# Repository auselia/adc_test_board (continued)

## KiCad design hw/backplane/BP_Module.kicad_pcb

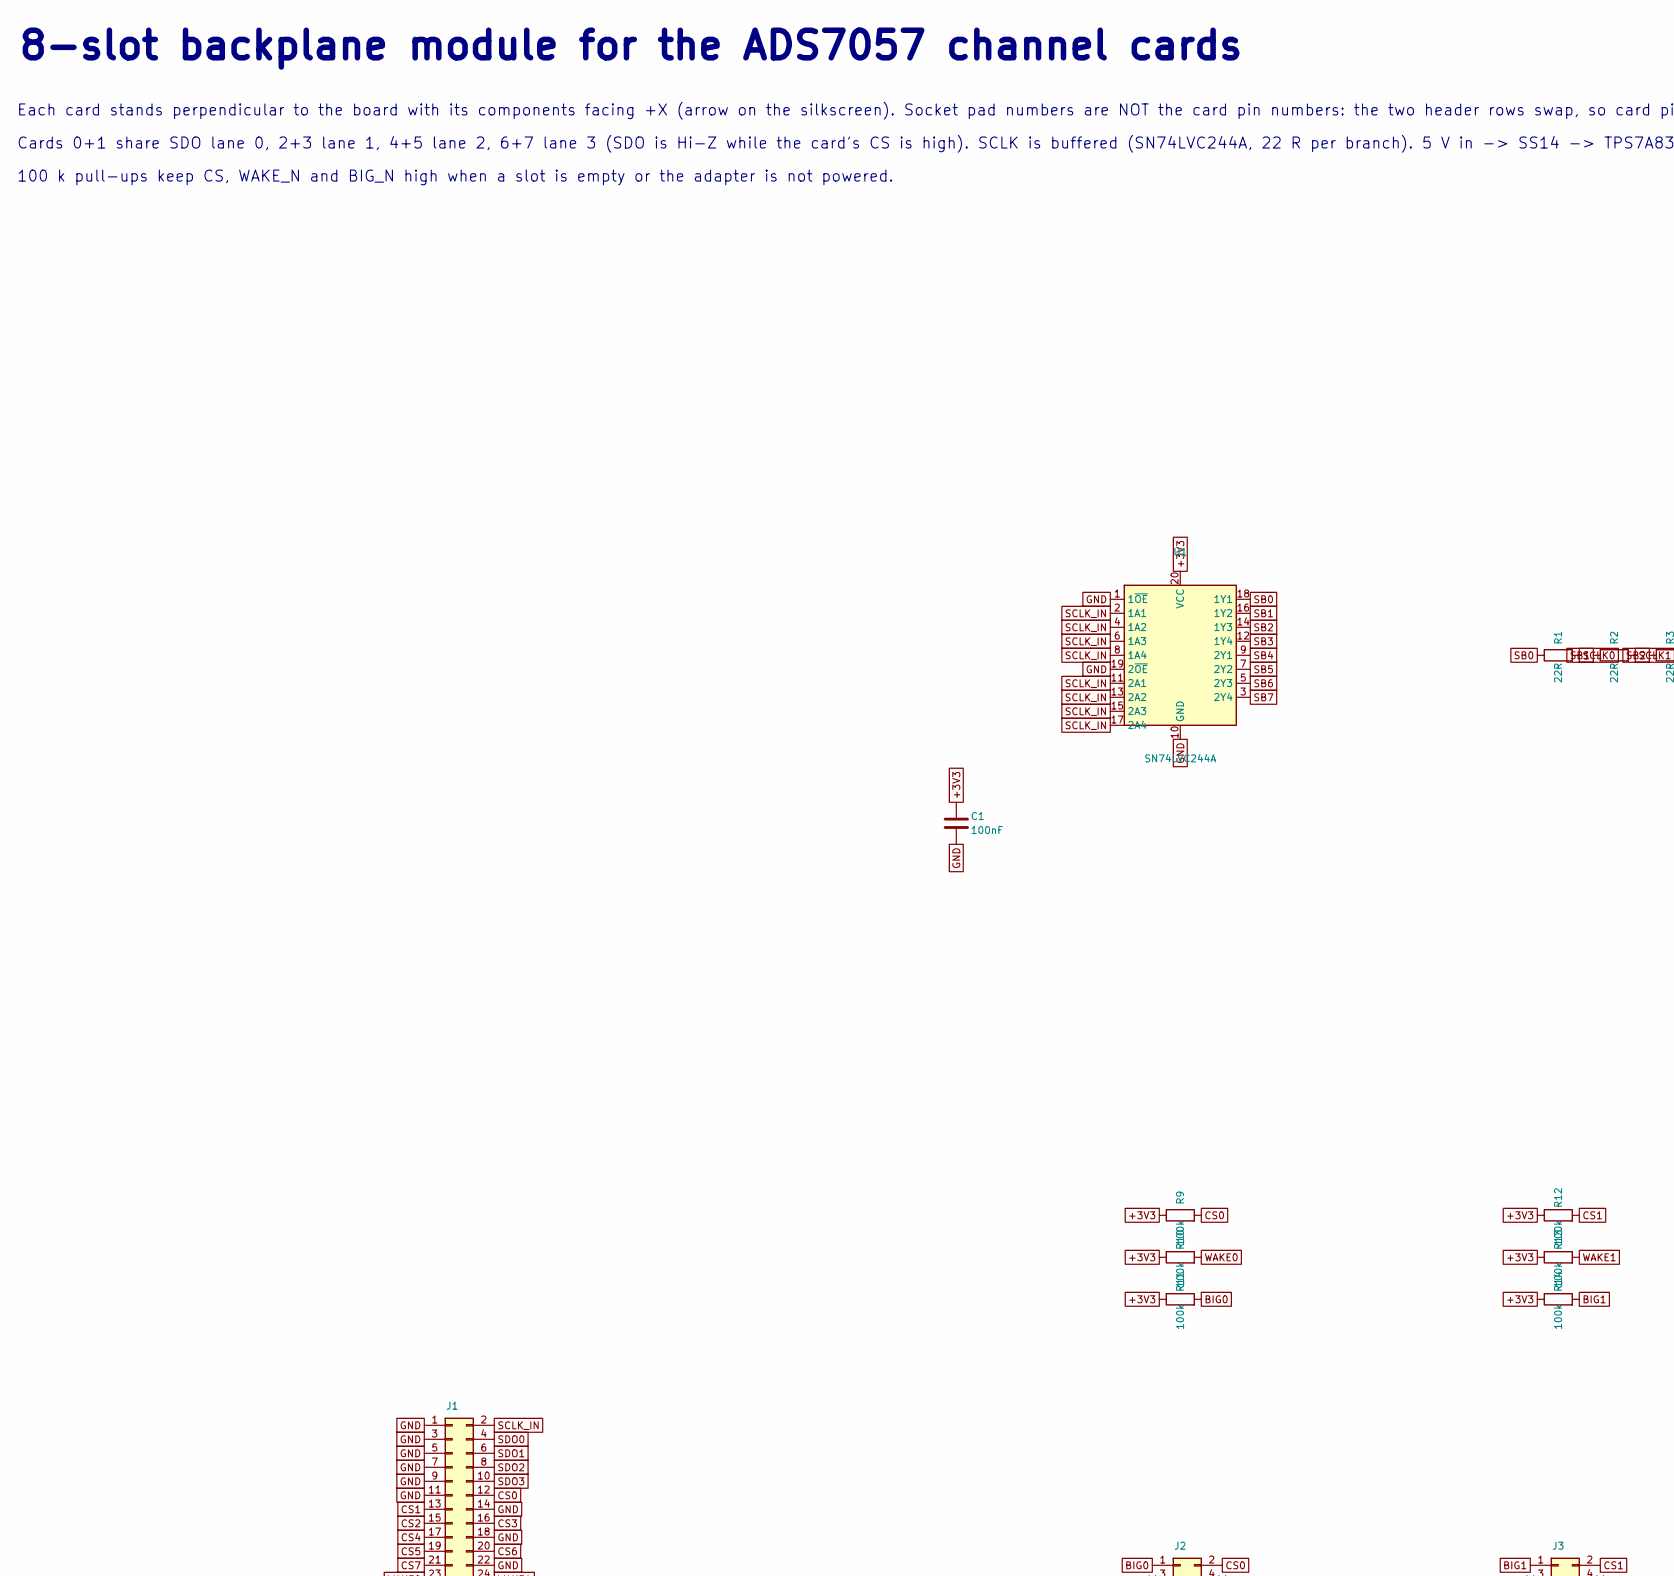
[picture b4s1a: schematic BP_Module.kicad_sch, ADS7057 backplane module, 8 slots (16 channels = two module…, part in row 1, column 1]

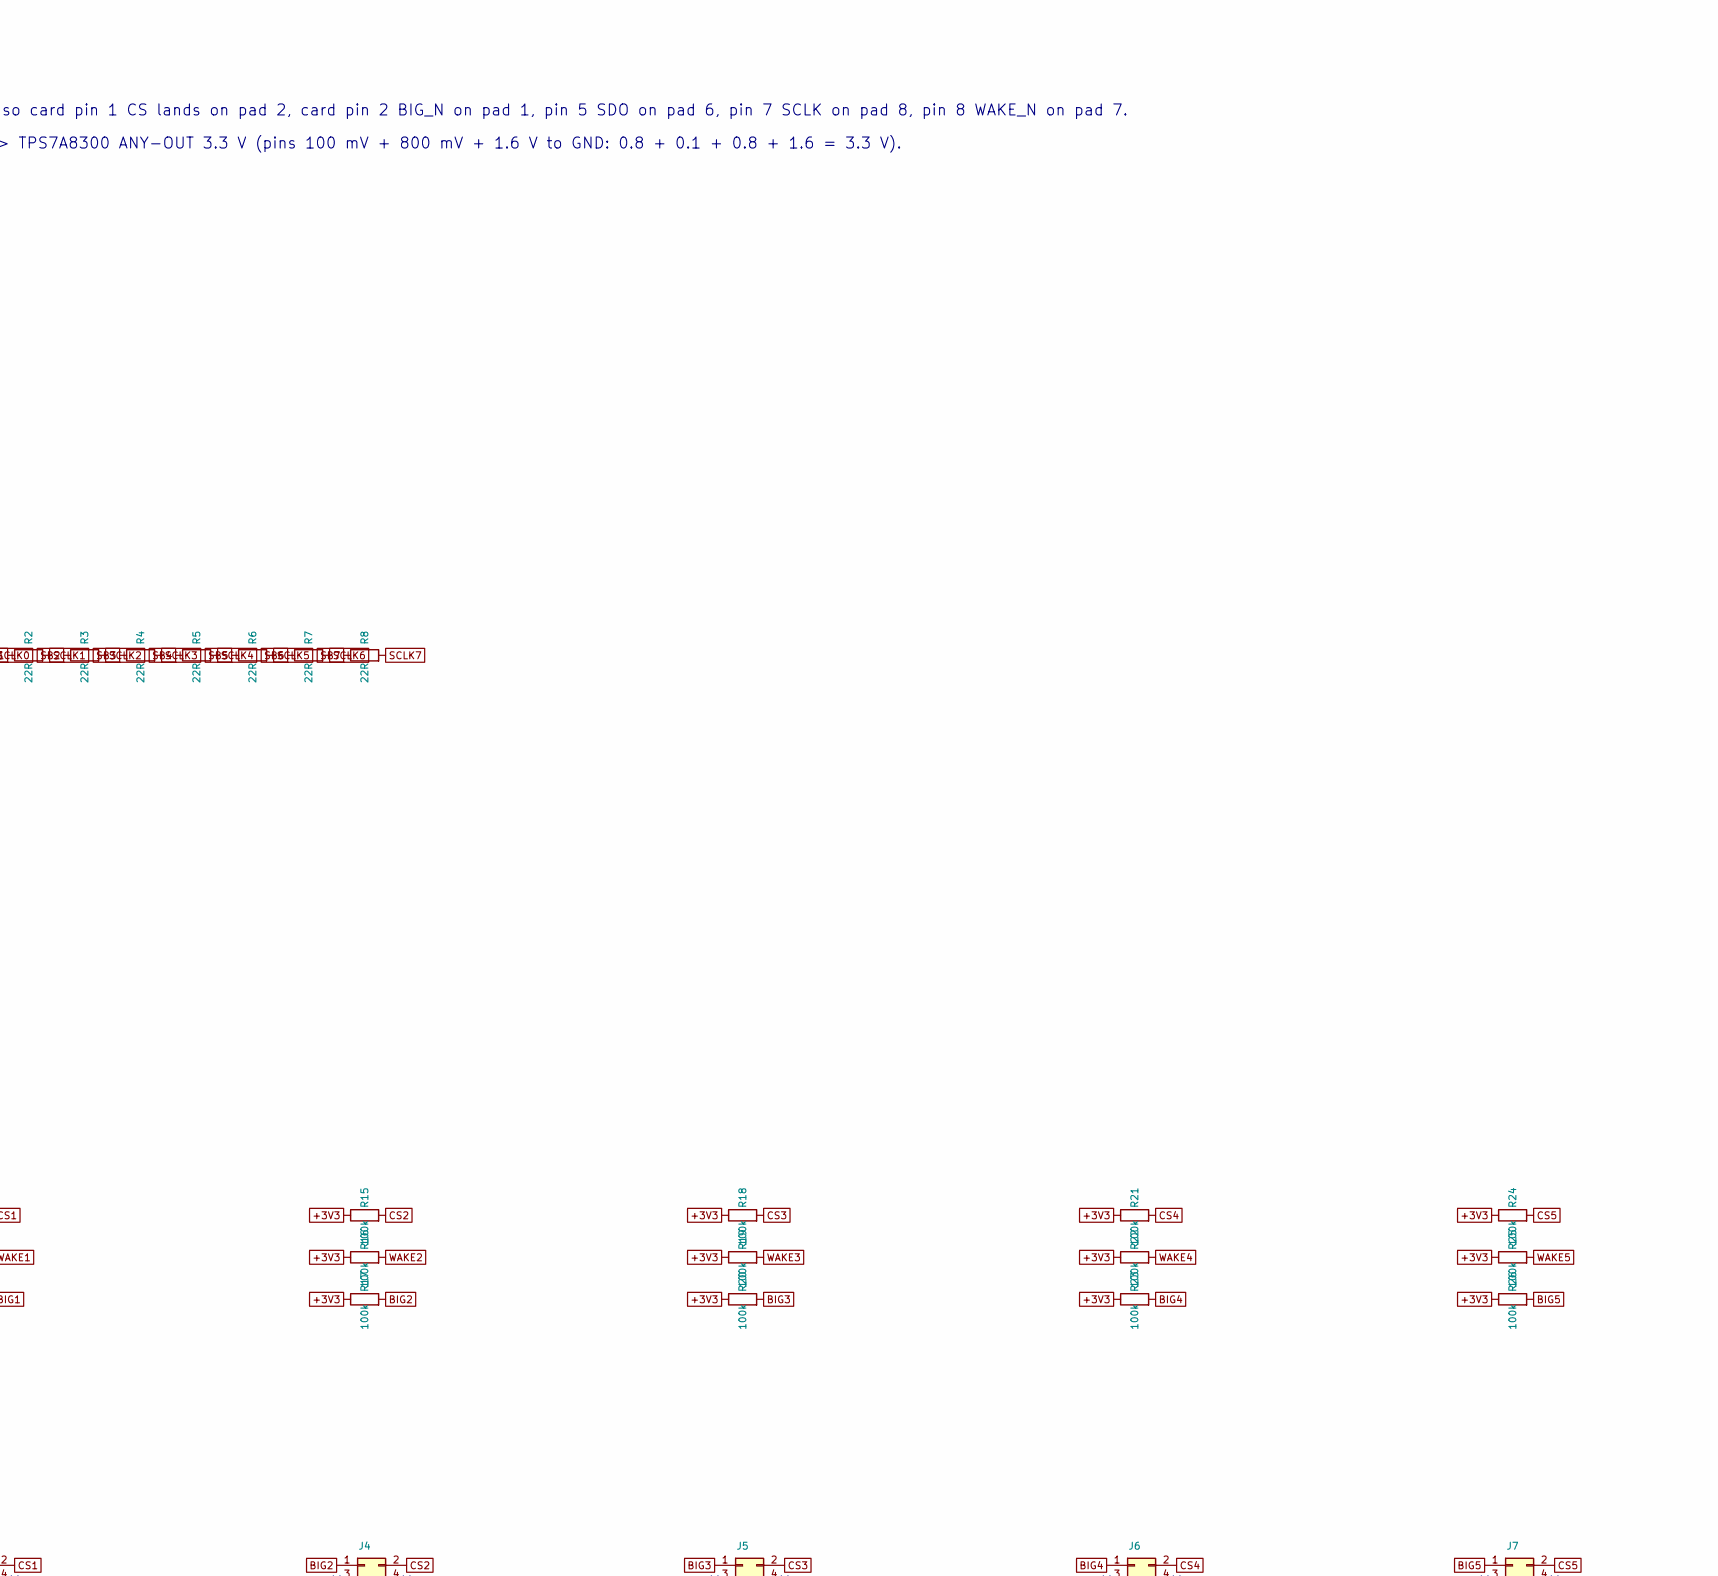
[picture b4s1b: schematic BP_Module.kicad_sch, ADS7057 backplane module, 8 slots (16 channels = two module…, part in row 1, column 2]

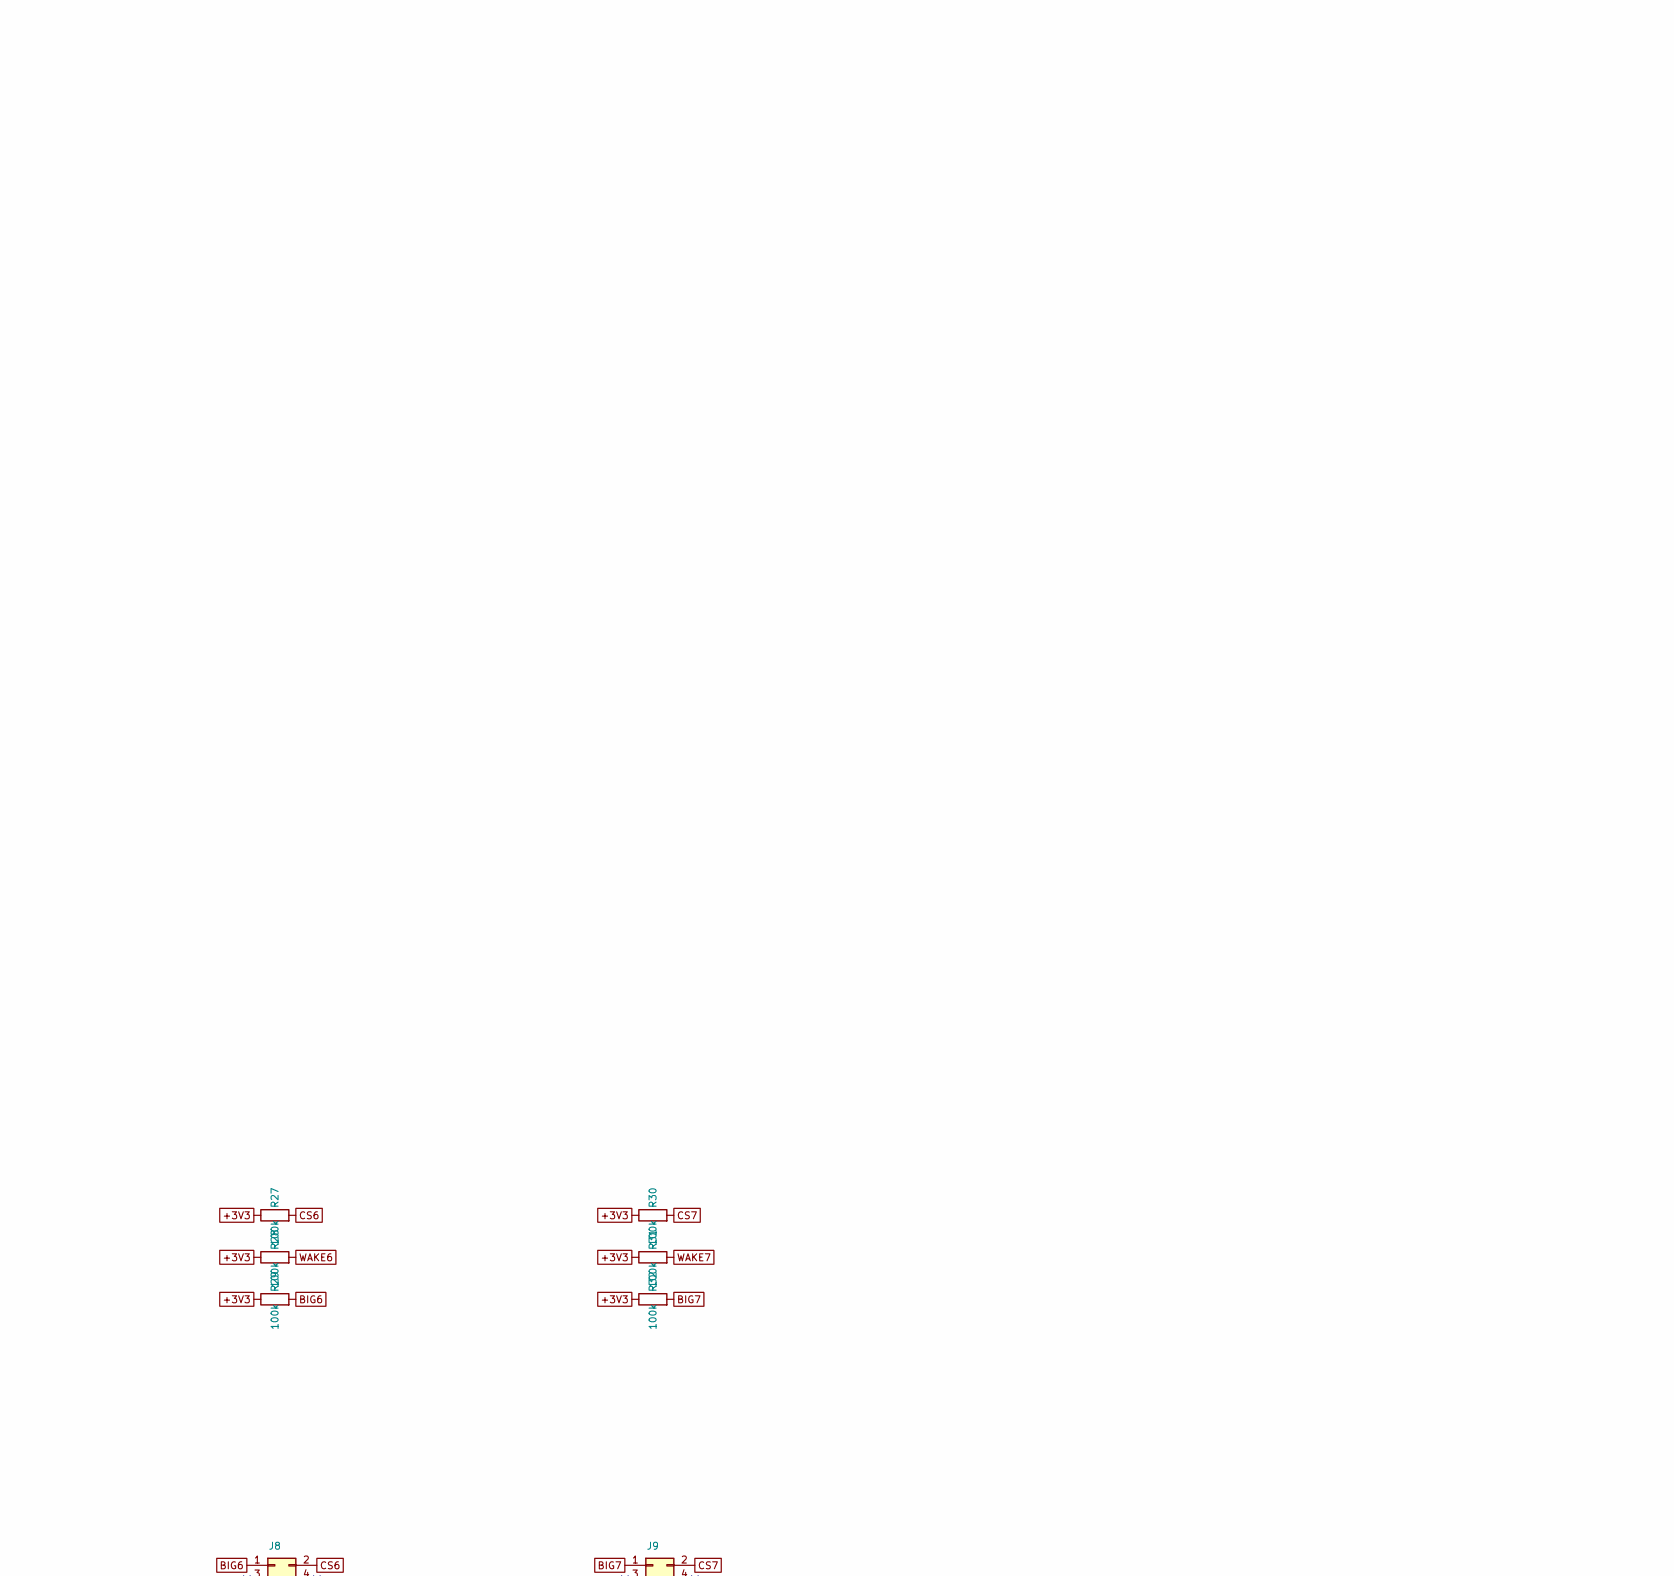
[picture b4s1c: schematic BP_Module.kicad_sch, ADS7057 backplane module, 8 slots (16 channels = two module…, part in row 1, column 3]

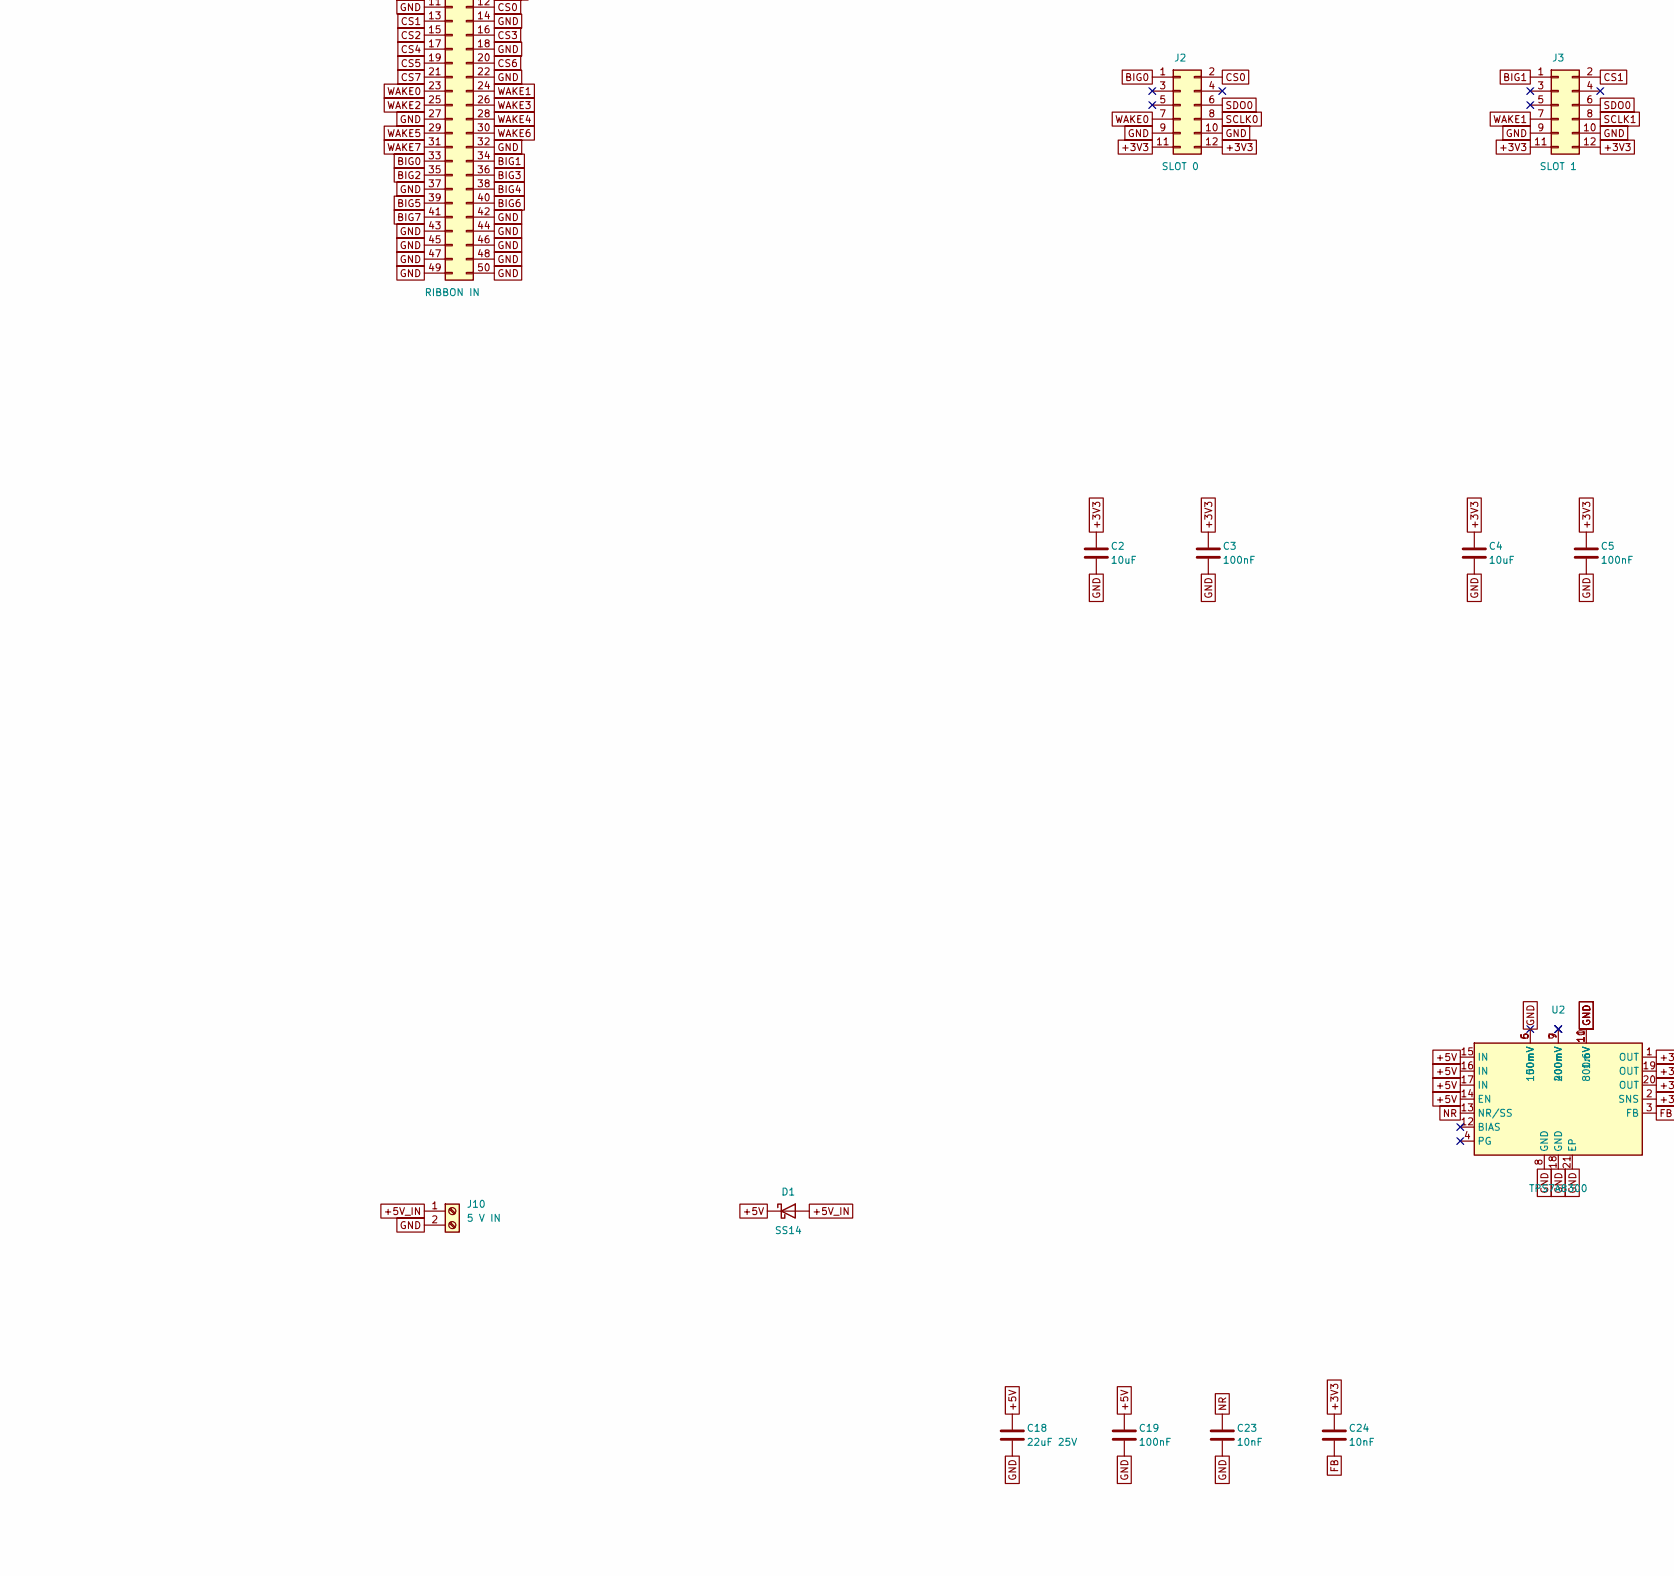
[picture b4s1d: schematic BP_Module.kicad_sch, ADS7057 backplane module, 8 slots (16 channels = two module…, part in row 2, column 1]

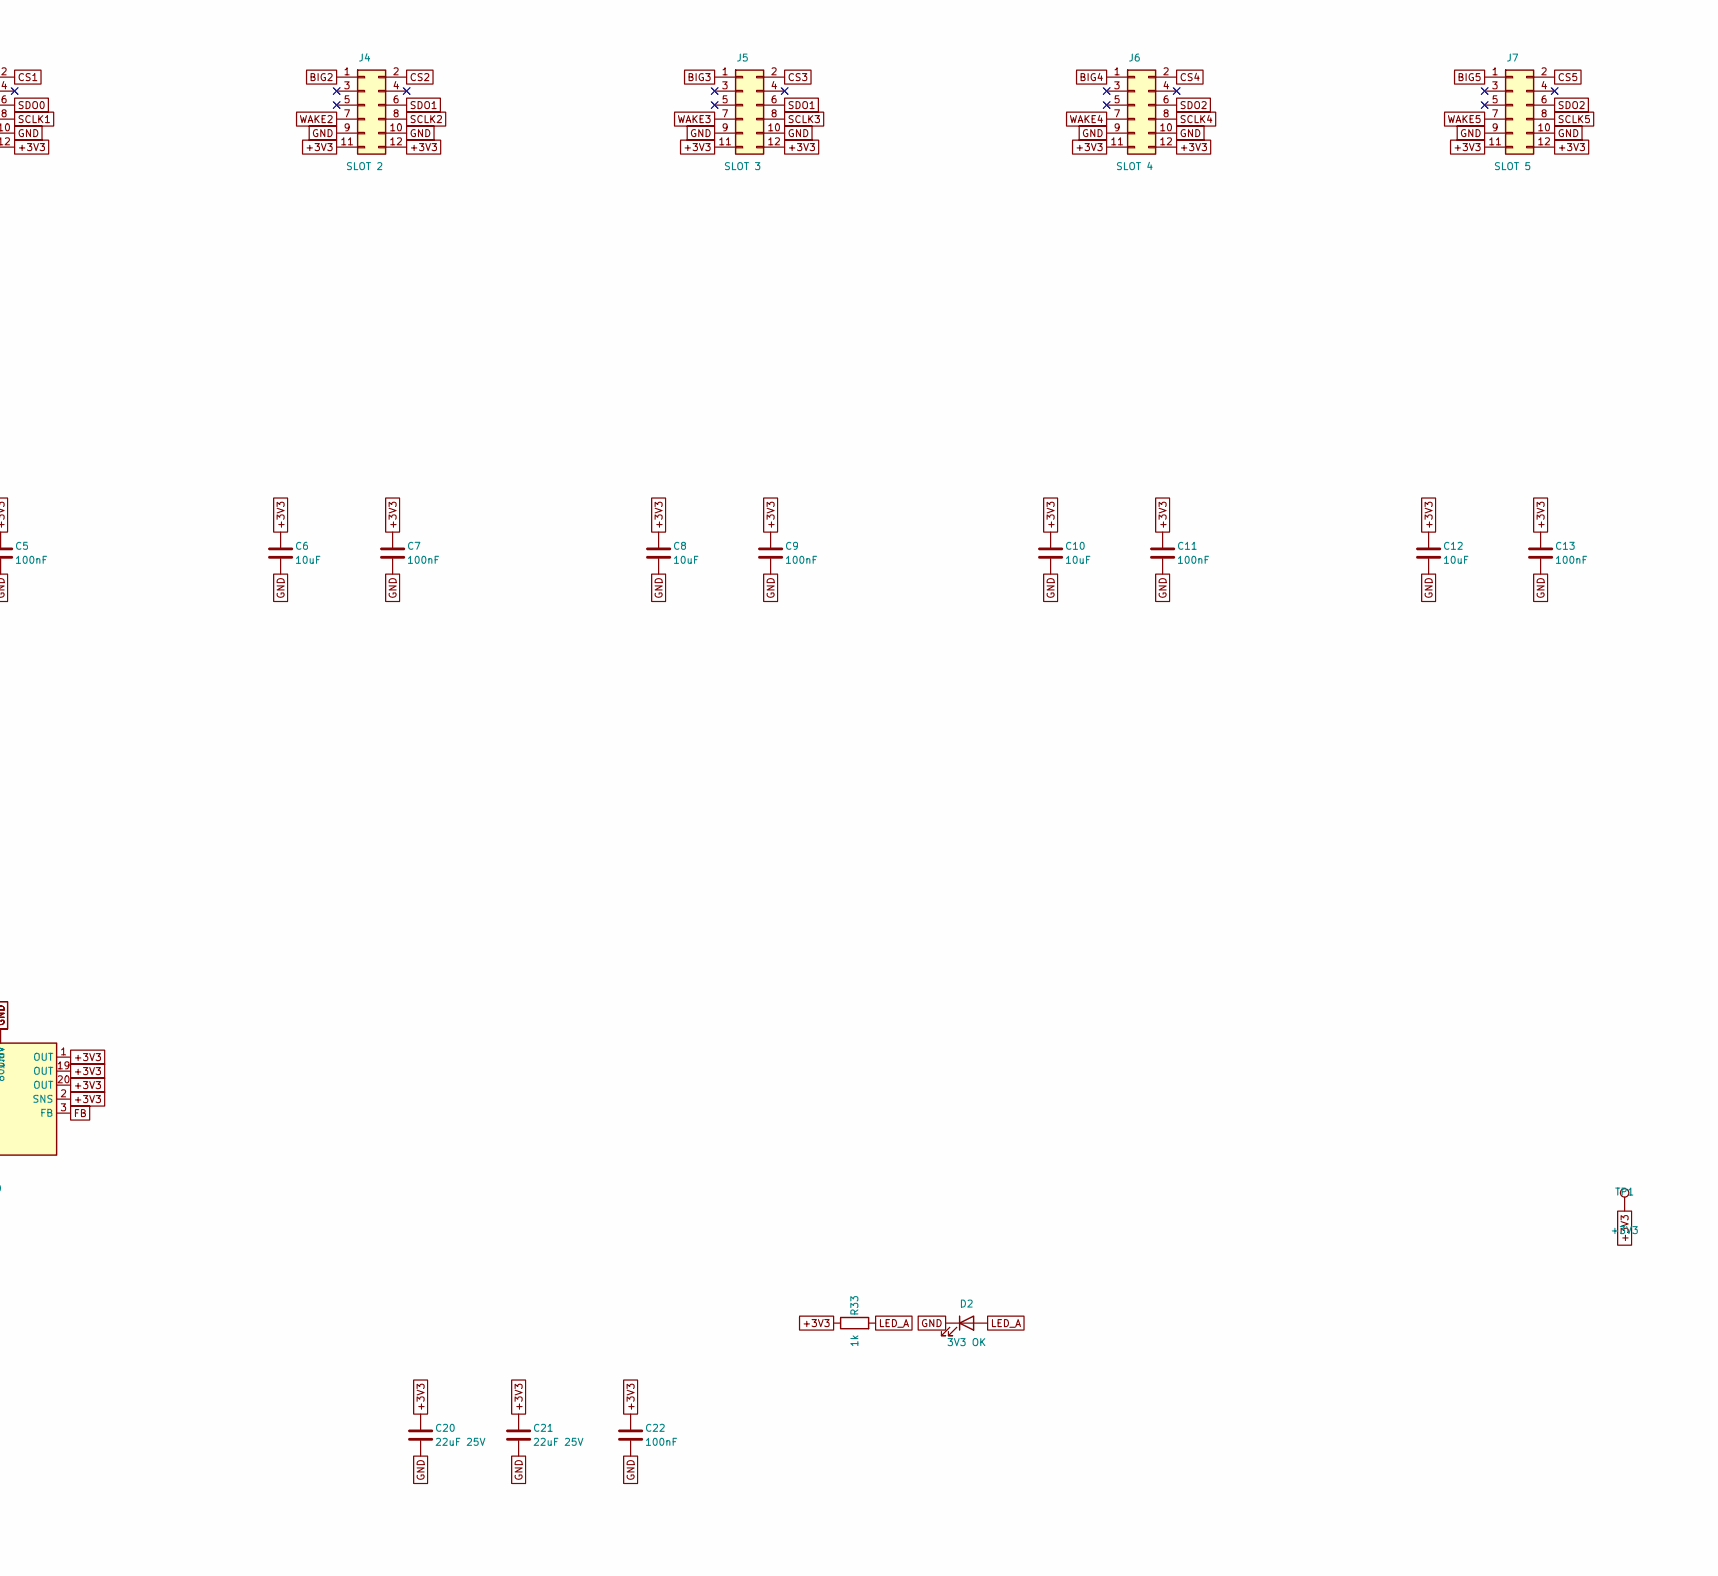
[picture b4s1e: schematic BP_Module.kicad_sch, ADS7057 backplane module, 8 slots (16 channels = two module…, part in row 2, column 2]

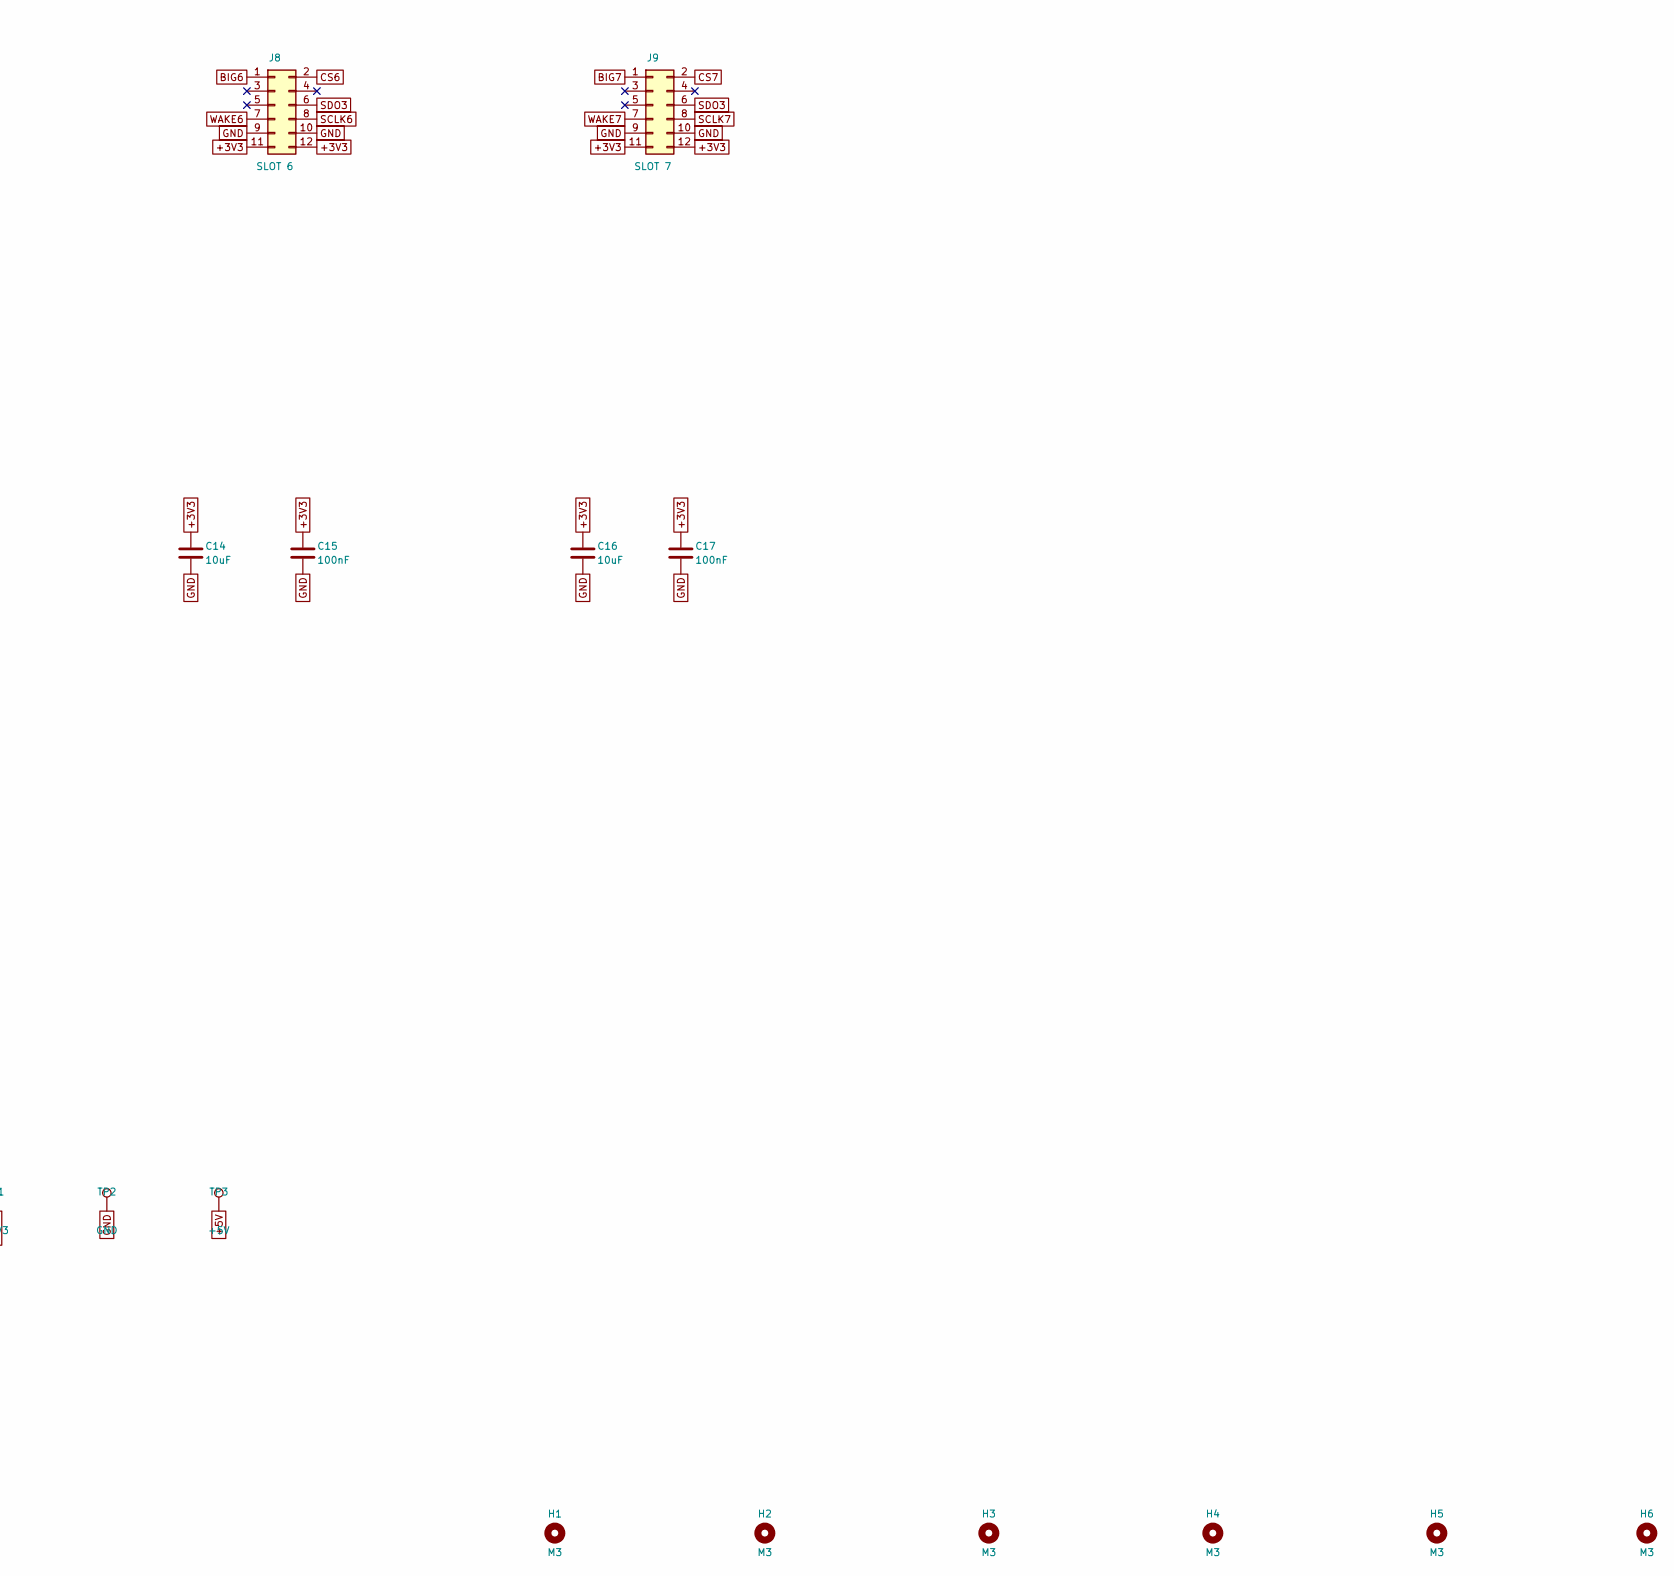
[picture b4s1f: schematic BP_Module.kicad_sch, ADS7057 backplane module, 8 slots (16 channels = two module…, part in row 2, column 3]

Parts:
C1, C3, C5, C7, C9, C11, C13, C15, C17, C19, C22: 100nF; C_0603_1608Metric; LCSC C14663
C2, C4, C6, C8, C10, C12, C14, C16: 10uF; C_0603_1608Metric; LCSC C19702
C18, C20, C21: 22uF 25V; C_0805_2012Metric; LCSC C45783
C23, C24: 10nF; C_0603_1608Metric; LCSC C57112
D1: SS14; D_SMA; LCSC C2480
D2: 3V3 OK; LED_0603_1608Metric; LCSC C2286
H1, H2, H3, H4, H5, H6: M3; MountingHole_3.2mm_M3
J1: RIBBON IN; IDC-Header_2x25_P2.54mm_Vertical; LCSC C19193816
J2: SLOT 0; PinSocket_2x06_P2.54mm_Vertical; LCSC C36191
J3: SLOT 1; PinSocket_2x06_P2.54mm_Vertical; LCSC C36191
J4: SLOT 2; PinSocket_2x06_P2.54mm_Vertical; LCSC C36191
J5: SLOT 3; PinSocket_2x06_P2.54mm_Vertical; LCSC C36191
J6: SLOT 4; PinSocket_2x06_P2.54mm_Vertical; LCSC C36191
J7: SLOT 5; PinSocket_2x06_P2.54mm_Vertical; LCSC C36191
J8: SLOT 6; PinSocket_2x06_P2.54mm_Vertical; LCSC C36191
J9: SLOT 7; PinSocket_2x06_P2.54mm_Vertical; LCSC C36191
J10: 5 V IN; TerminalBlock_Phoenix_MKDS-1,5-2-5.08_1x02_P5.08mm_Horizont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; LCSC C8465
R1, R2, R3, R4, R5, R6, R7, R8: 22R; R_0603_1608Metric; LCSC C23345
R9, R10, R11, R12, R13, R14, R15, R16, R17, R18, R19, R20, R21, R22, R23, R24, R25, R26, R27, R28, R29, R30, R31, R32: 100k; R_0603_1608Metric; LCSC C25803
R33: 1k; R_0603_1608Metric; LCSC C21190
TP1: +3V3; TestPoint_Pad_D1.5mm
TP2: GND; TestPoint_Pad_D1.5mm
TP3: +5V; TestPoint_Pad_D1.5mm
U1: SN74LVC244A; TSSOP-20_4.4x6.5mm_P0.65mm; LCSC C7668
U2: TPS7A8300; QFN-20-1EP_3.5x3.5mm_P0.5mm_EP2x2mm; LCSC C544500

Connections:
+3V3: C1.1, C2.1, C3.1, C4.1, C5.1, C6.1, C7.1, C8.1, C9.1, C10.1, C11.1, C12.1, C13.1, C14.1, C15.1, C16.1, C17.1, C20.1, C21.1, C22.1, C24.1, J2.11, J2.12, J3.11, J3.12, J4.11, J4.12, J5.11, J5.12, J6.11, J6.12, J7.11, J7.12, J8.11, J8.12, J9.11, J9.12, R9.1, R10.1, R11.1, R12.1, R13.1, R14.1, R15.1, R16.1, R17.1, R18.1, R19.1, R20.1, R21.1, R22.1, R23.1, R24.1, R25.1, R26.1, R27.1, R28.1, R29.1, R30.1, R31.1, R32.1, R33.1, TP1.1, U1.20 (VCC), U2.1 (OUT), U2.2 (SNS), U2.19 (OUT), U2.20 (OUT)
+5V: C18.1, C19.1, D1.1 (K), TP3.1, U2.14 (EN), U2.15 (IN), U2.16 (IN), U2.17 (IN)
+5V_IN: D1.2 (A), J10.1
BIG0: J1.33, J2.1, R11.2
BIG1: J1.34, J3.1, R14.2
BIG2: J1.35, J4.1, R17.2
BIG3: J1.36, J5.1, R20.2
BIG4: J1.38, J6.1, R23.2
BIG5: J1.39, J7.1, R26.2
BIG6: J1.40, J8.1, R29.2
BIG7: J1.41, J9.1, R32.2
CS0: J1.12, J2.2, R9.2
CS1: J1.13, J3.2, R12.2
CS2: J1.15, J4.2, R15.2
CS3: J1.16, J5.2, R18.2
CS4: J1.17, J6.2, R21.2
CS5: J1.19, J7.2, R24.2
CS6: J1.20, J8.2, R27.2
CS7: J1.21, J9.2, R30.2
FB: C24.2, U2.3 (FB)
GND: C1.2, C2.2, C3.2, C4.2, C5.2, C6.2, C7.2, C8.2, C9.2, C10.2, C11.2, C12.2, C13.2, C14.2, C15.2, C16.2, C17.2, C18.2, C19.2, C20.2, C21.2, C22.2, C23.2, D2.1 (K), J1.1, J1.3, J1.5, J1.7, J1.9, J1.11, J1.14, J1.18, J1.22, J1.27, J1.32, J1.37, J1.42, J1.43, J1.44, J1.45, J1.46, J1.47, J1.48, J1.49, J1.50, J2.9, J2.10, J3.9, J3.10, J4.9, J4.10, J5.9, J5.10, J6.9, J6.10, J7.9, J7.10, J8.9, J8.10, J9.9, J9.10, J10.2, TP2.1, U1.1 (1~OE), U1.10 (GND), U1.19 (2~OE), U2.5 (50mV), U2.6 (100mV), U2.8 (GND), U2.10 (800mV), U2.11 (1.6V), U2.18 (GND), U2.21 (EP)
LED_A: D2.2 (A), R33.2
NR: C23.1, U2.13 (NR/SS)
SB0: R1.1, U1.18 (1Y1)
SB1: R2.1, U1.16 (1Y2)
SB2: R3.1, U1.14 (1Y3)
SB3: R4.1, U1.12 (1Y4)
SB4: R5.1, U1.9 (2Y1)
SB5: R6.1, U1.7 (2Y2)
SB6: R7.1, U1.5 (2Y3)
SB7: R8.1, U1.3 (2Y4)
SCLK0: J2.8, R1.2
SCLK1: J3.8, R2.2
SCLK2: J4.8, R3.2
SCLK3: J5.8, R4.2
SCLK4: J6.8, R5.2
SCLK5: J7.8, R6.2
SCLK6: J8.8, R7.2
SCLK7: J9.8, R8.2
SCLK_IN: J1.2, U1.2 (1A1), U1.4 (1A2), U1.6 (1A3), U1.8 (1A4), U1.11 (2A1), U1.13 (2A2), U1.15 (2A3), U1.17 (2A4)
SDO0: J1.4, J2.6, J3.6
SDO1: J1.6, J4.6, J5.6
SDO2: J1.8, J6.6, J7.6
SDO3: J1.10, J8.6, J9.6
WAKE0: J1.23, J2.7, R10.2
WAKE1: J1.24, J3.7, R13.2
WAKE2: J1.25, J4.7, R16.2
WAKE3: J1.26, J5.7, R19.2
WAKE4: J1.28, J6.7, R22.2
WAKE5: J1.29, J7.7, R25.2
WAKE6: J1.30, J8.7, R28.2
WAKE7: J1.31, J9.7, R31.2

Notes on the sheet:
8-slot backplane module for the ADS7057 channel cards
Each card stands perpendicular to the board with its components facing +X (arrow on the silkscreen). Socket pad numbers are NOT the card pin numbers: the two header rows swap, so card pin 1 CS lands on pad 2, card pin 2 BIG_N on pad 1, pin 5 SDO on pad 6, pin 7 SCLK on pad 8, pin 8 WAKE_N on pad 7.
Cards 0+1 share SDO lane 0, 2+3 lane 1, 4+5 lane 2, 6+7 lane 3 (SDO is Hi-Z while the card's CS is high). SCLK is buffered (SN74LVC244A, 22 R per branch). 5 V in -> SS14 -> TPS7A8300 ANY-OUT 3.3 V (pins 100 mV + 800 mV + 1.6 V to GND: 0.8 + 0.1 + 0.8 + 1.6 = 3.3 V).
100 k pull-ups keep CS, WAKE_N and BIG_N high when a slot is empty or the adapter is not powered.

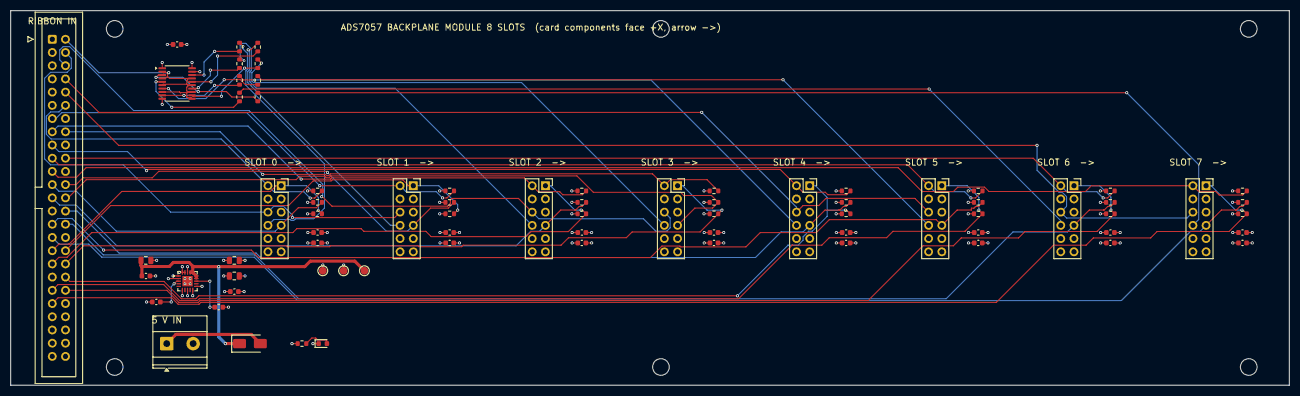
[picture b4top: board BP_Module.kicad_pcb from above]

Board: 4 copper layers, 245.8 x 72.0 mm, 80 parts (0 on the bottom side), 52 nets.

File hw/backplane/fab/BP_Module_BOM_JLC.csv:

Comment,Designator,Footprint,LCSC Part #
100nF,"C1,C3,C5,C7,C9,C11,C13,C15,C17,C19,C22",C_0603_1608Metric,C14663
10uF,"C2,C4,C6,C8,C10,C12,C14,C16",C_0603_1608Metric,C19702
22uF 25V,"C18,C20,C21",C_0805_2012Metric,C45783
10nF,"C23,C24",C_0603_1608Metric,C57112
SS14,D1,D_SMA,C2480
3V3 OK,D2,LED_0603_1608Metric,C2286
IDC box header 2x25,J1,IDC-Header_2x25_P2.54mm_Vertical,C19193816
Socket 2x6 2.54 mm,"J2,J3,J4,J5,J6,J7,J8,J9",PinSocket_2x06_P2.54mm_Vertical,C36191
Screw terminal 5.08 mm 2P,J10,"TerminalBlock_Phoenix_MKDS-1,5-2-5.08_1x02_P5.08mm_Horizontal",C8465
22R,"R1,R2,R3,R4,R5,R6,R7,R8",R_0603_1608Metric,C23345
100k,"R9,R10,R11,R12,R13,R14,R15,R16,R17,R18,R19,R20,R21,R22,R23,R24,R25,R26,R27,R28,R29,R30,R31,R32",R_0603_1608Metric,C25803
1k,R33,R_0603_1608Metric,C21190
SN74LVC244A,U1,TSSOP-20_4.4x6.5mm_P0.65mm,C7668
TPS7A8300,U2,QFN-20-1EP_3.5x3.5mm_P0.5mm_EP2x2mm,C544500

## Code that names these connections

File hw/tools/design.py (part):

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    C(sh,215,255,'4.7uF','AVDD','GND','C18'); C(sh,255,255,'1uF','+3V3','GND','C19'); C(sh,270,255,'100nF','+3V3','GND','C20')
    R(sh,280,195,'22R','CS','CS_A','R18',90); R(sh,280,210,'22R','SCLK','SCLK_A','R19',90); R(sh,280,225,'22R','SDO_A','SDO','R20',90)
    # ---- AVDD: the 3.3 V rail through a 10 ohm / 10 uF filter (no regulator: the rail is already 3.3 V)
    text(sh,"AVDD = +3V3_C through R34 10R and C21 10 uF. C18 4.7 uF + C22 100 nF sit at the ADS7057 AVDD pin. DVDD = +3V3.",300,170,2.2,True)
    R(sh,350,205,'10R','+3V3_C','AVDD','R34',90); C(sh,360,235,'10uF','AVDD','GND','C21'); C(sh,375,235,'100nF','AVDD','GND','C22')
    # ---- listener: passive band-pass on SIG_IN, two window comparators (WAKE_N small, BIG_N large), open drain
    text(sh,"Listener (observer, never gates the chain). SIG_IN -> C40 100 pF / R35 10k to REFL (159 kHz high-pass) -> R36 10k / C41 22 pF (723 kHz low-pass, light load on the high-pass) -> LST.",20,275,1.8)
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    for k_,(ref_,net_) in enumerate(TPS):
        add(sh,'Connector:TestPoint',net_,FP_TP,20+k_*11,408,{'1':net_},'TP',ref=ref_)
    # ---- ZedBoard PMOD (Digilent type 2A SPI: 1 CS, 2 MOSI, 3 MISO, 4 SCK, 5 GND, 6 VCC; 7..10 extra I/O)
    text(sh,"ZedBoard PMOD JA..JD (3.3 V). Pin 6/12 = 3.3 V from the ZedBoard = the board's only supply. Pin 10 = WAKE_N, pin 7 = BIG_N (active low).",330,55,2.2,True)
    pm={'1':'CS','3':'NC','5':'SDO','7':'SCLK','9':'GND','11':'+3V3_PMOD',     # PMOD pins 1..6 (top row)
        '2':'BIG_N','4':'NC','6':'NC','8':'WAKE_N','10':'GND','12':'+3V3_PMOD'}     # PMOD pins 7..12 (bottom row)
    add(sh,'Connector_Generic:Conn_02x06_Odd_Even','PMOD (ZedBoard)',FP_PMOD,370,90,pm,'J',ref='J3',props={'LCSC':'C60565'})
    text(sh,"MON: LPF_OUT through 51R to an SMA for the scope (same signal the ADC samples).",480,55,2.2,True)
    R(sh,490,90,'51R','LPF_OUT','MON','R25',90)
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    add(sh,'Mechanical:MountingHole','M2','MountingHole:MountingHole_2.2mm_M2',540,150,{},'H',ref='H4')
    # ---- SENSOR IN (J1): bias-T. +5 V through R26/L2 onto the coax centre = power for the sensor head; C33 passes its signal to SIG_IN.
    text(sh,"SENSOR IN (J1) = bias-T for the sensor head. +3V3 -> 47R (R26, C32 filter) -> JP1 -> 470 uH (L2) -> coax centre. C33 100 nF passes the head's signal to SIG_IN.",20,360,1.8,True)
    text(sh,"R27 1M gives SIG_IN a DC level (VMID5). To feed a function generator or a perfboard instead, cut the solder jumper JP1 (bridged by a copper trace) so the centre pin carries no DC.",20,366,1.8)
    add(sh,'Device:L','470uH',FP_L,80,390,{'1':'HEAD_LINE','2':'HEAD_PWR_L'},'L',rot=90,ref='L2',props={'LCSC':LCSC['470uH']})
    add(sh,'Jumper:SolderJumper_2_Bridged','HEAD PWR',FP_JP,95,390,{'1':'HEAD_PWR','2':'HEAD_PWR_L'},'JP',rot=90,ref='JP1')
    R(sh,110,380,'47R','+3V3','HEAD_PWR','R26',90); C(sh,130,400,'10uF','HEAD_PWR','GND','C32')
    C(sh,150,380,'100nF','HEAD_LINE','SIG_IN','C33',90); R(sh,170,400,'1M','SIG_IN','VMID5','R27',0)
    # ---- SENSOR HEAD (separate 10 x 20 mm board in the same panel): perfboard charge amp, powered through the coax
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    text(sh,"SOT-23-5 for OPA365 or OPA314 (same pinout), VREF = V+/2 (1M/1M + 10 uF, 1.6 uA), all 0402. Head ground is HGND (a separate board).",220,366,1.8)
    add(sh,'Connector:TestPoint','PIEZO +',FP_PZ,225,380,{'1':'HSUM'},'TP',ref='TP1')
    add(sh,'Connector:TestPoint','PIEZO -',FP_PZ,225,392,{'1':'HGND'},'TP',ref='TP2')
    add(sh,'Auselia:OPA365','OPA365','Package_TO_SOT_SMD:SOT-23-5',290,390,{'3':'HREF','4':'HSUM','1':'HOUT','5':'HV','2':'HGND'},'U',ref='U8',props={'LCSC':'C96626'})
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
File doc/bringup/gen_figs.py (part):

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# ---- 4. expected waveforms (120 mV burst, simulation)
b=S['burst']['0.12']; t=np.array(b['t'])*1e6
fig,axs=plt.subplots(1,2,figsize=(7.4,2.8))
ax=axs[0]; ax.plot(t,np.array(b['gout']),color=GRN,lw=1.6,label='TP5 GAIN_OUT'); ax.plot(t,np.array(b['lpf']),color=AMB,lw=1.4,label='TP6 LPF_OUT'); ax.axhline(1.65,color=MUT,lw=0.7,ls=':')
ax.set_xlabel('time (us)'); ax.set_ylabel('volts'); ax.set_ylim(1.0,2.7); ax.set_title('Chain, 120 mV peak burst at 250 kHz',fontsize=8.5,loc='left'); ax.legend(fontsize=7,frameon=False,ncol=2,loc='upper left')
ax=axs[1]; ax.plot(t,np.array(b['op']),color=BLU,lw=1.4,label='TP7 DRV+'); ax.plot(t,np.array(b['om']),color=PNK,lw=1.4,label='TP8 DRV-'); ax.plot(t,np.array(b['adc'])+1.65,color=RED,lw=1.0,ls='--',label='difference (shifted)'); ax.axhline(1.65,color=MUT,lw=0.7,ls=':')
ax.set_xlabel('time (us)'); ax.set_ylim(1.0,2.7); ax.set_title('Driver outputs',fontsize=8.5,loc='left'); ax.legend(fontsize=7,frameon=False,ncol=3,loc='upper left')
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fig,ax=plt.subplots(figsize=(7.2,2.6)); ks=list(g)[::-1]
ax.barh(range(len(ks)),[g[k] for k in ks],color=[GRN if 'SIG' in k else AMB if 'ADC' in k else '#5a8f78' for k in ks],height=0.6)
for y,k in enumerate(ks): ax.text(g[k]+0.06,y,'x %.2f'%g[k],va='center',fontsize=8)
ax.set_yticks(range(len(ks))); ax.set_yticklabels(ks,fontsize=8); ax.set_xlim(0,5.2); ax.set_xlabel('amplitude relative to SIG_IN, 250 kHz (peak of the AC part)',fontsize=8)
for s in ax.spines.values(): s.set_color(MUT)
ax.grid(axis='x',color='#d3dacf',lw=0.4); save(fig,'fig_ladder')
print(g)
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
